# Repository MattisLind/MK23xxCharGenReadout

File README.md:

# Mostek MK23XX Character Generator Readout

This device is used to read out the contents of early character generator MK23XX ROMs from Mostek. These devices is a bit special since they include a column counter so that the each column cannot be
accessed directly through external addressing pins.

The device has to be connected over USB (unless this section is commented out in the source code) and then it provide a dump of the contents of the ROM as hex as it cycles through all 64 characters.

```
CHAR0 COLUMN 0 VALUE 0
CHAR0 COLUMN 1 VALUE 0
CHAR0 COLUMN 2 VALUE 0
CHAR0 COLUMN 3 VALUE 0
CHAR0 COLUMN 4 VALUE 0
CHAR1 COLUMN 0 VALUE 7
CHAR1 COLUMN 1 VALUE 7
CHAR1 COLUMN 2 VALUE 7
CHAR1 COLUMN 3 VALUE 7
CHAR1 COLUMN 4 VALUE 7
CHAR2 COLUMN 0 VALUE 70
CHAR2 COLUMN 1 VALUE 70
CHAR2 COLUMN 2 VALUE 70
CHAR2 COLUMN 3 VALUE 70
CHAR2 COLUMN 4 VALUE 70
```

Please note that the contents of this example ROM is active low so that a binary 0 indicate a lit pixel. Depending if the outputs are active low or high the output driver can be 7407 or 7406 respectively.

## PCB

The first PCB had too small holes for the 24 pin ROM socket so it was not possible to fit a ZIF socket. I revised the PCB so that the new PCB have 1.0 mm holes rather than 0.8 mm. I think that this should work better but have not ordered any PCB to check. 

## Software

The software is an Arduino sketch. I have been using [Arduino Core STM32](https://github.com/stm32duino/Arduino_Core_STM32) library. The Bluepill is a STM32F103C6 and it is set to have USB enabled with serial support 

There is a #define SCROLL which can be set to either 0 or 1 if one want the fancier soft scroll rather than just showing each character.

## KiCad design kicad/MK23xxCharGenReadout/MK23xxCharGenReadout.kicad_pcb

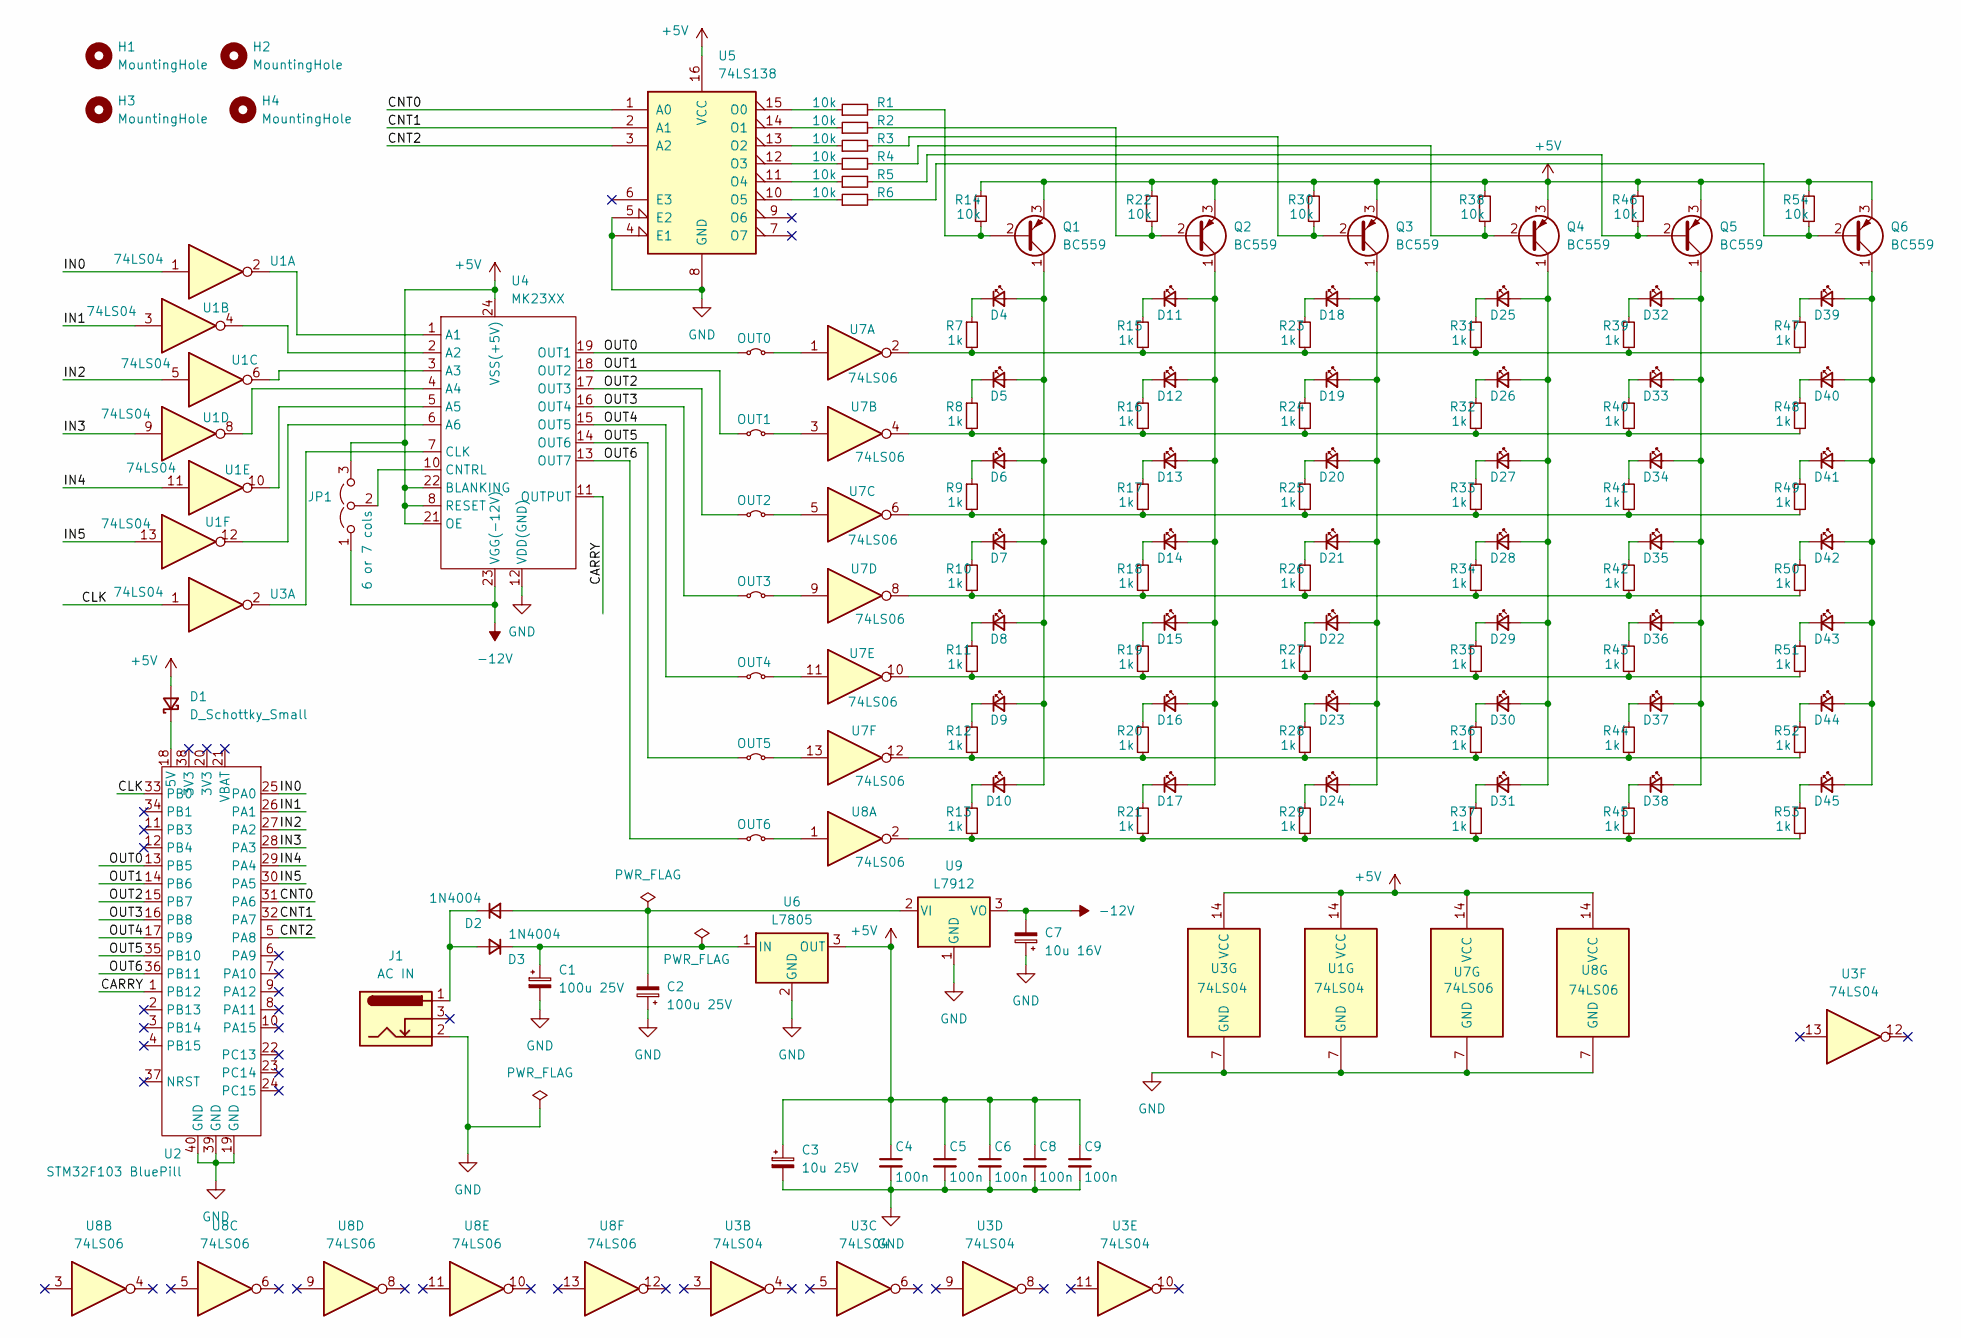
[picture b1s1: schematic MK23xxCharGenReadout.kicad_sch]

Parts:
C1, C2: 100u 25V; CP_Radial_D8.0mm_P5.00mm
C3: 10u 25V; CP_Radial_D7.5mm_P2.50mm
C4, C5, C6, C8, C9: 100n; C_Disc_D5.0mm_W2.5mm_P5.00mm
C7: 10u 16V; CP_Radial_D7.5mm_P2.50mm
D1: D_Schottky_Small; D_DO-41_SOD81_P10.16mm_Horizontal
D2, D3: 1N4004; D_DO-41_SOD81_P10.16mm_Horizontal
D4, D5, D6, D7, D8, D9, D10, D11, D12, D13, D14, D15, D16, D17, D18, D19, D20, D21, D22, D23, D24, D25, D26, D27, D28, D29, D30, D31, D32, D33, D34, D35, D36, D37, D38, D39, D40, D41, D42, D43, D44, D45: LED_Small; LED_D5.0mm
H1, H2, H3, H4: MountingHole; MountingHole_3.2mm_M3
J1: AC IN; BarrelJack_Kycon_KLDX-0202-xC_Horizontal
JP1: 6 or 7 cols; PinHeader_1x03_P2.54mm_Vertical
OUT0, OUT1, OUT2, OUT3, OUT4, OUT5, OUT6: Jumper_2_Small_Bridged; PinHeader_1x02_P2.54mm_Vertical
Q1, Q2, Q3, Q4, Q5, Q6: BC559; TO-92
R1, R2, R3, R4, R5, R6, R14, R22, R30, R38, R46, R54: 10k; R_Axial_DIN0207_L6.3mm_D2.5mm_P7.62mm_Horizontal
R7, R8, R9, R10, R11, R12, R13, R15, R16, R17, R18, R19, R20, R21, R23, R24, R25, R26, R27, R28, R29, R31, R32, R33, R34, R35, R36, R37, R39, R40, R41, R42, R43, R44, R45, R47, R48, R49, R50, R51, R52, R53: 1k; R_Axial_DIN0207_L6.3mm_D2.5mm_P7.62mm_Horizontal
U1, U3: 74LS04; DIP-14_W7.62mm
U2: STM32F103 BluePill; DIP-40_W15.24mm
U4: MK23XX; DIP-24_W15.24mm
U5: 74LS138; DIP-16_W7.62mm
U6: L7805; TO-220-3_Vertical
U7, U8: 74LS06; DIP-14_W7.62mm
U9: L7912; TO-220-3_Vertical

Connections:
+5V: C3.1, C4.1, C5.1, C6.1, C8.1, C9.1, D1.2 (A), JP1.3 (B), Q1.3 (E), Q2.3 (E), Q3.3 (E), Q4.3 (E), Q5.3 (E), Q6.3 (E), R14.1, R22.1, R30.1, R38.1, R46.1, R54.1, U1.14 (VCC), U3.14 (VCC), U4.8 (RESET), U4.21 (OE), U4.22 (BLANKING), U4.24 (VSS(+5V)), U5.16 (VCC), U6.3 (OUT), U7.14 (VCC), U8.14 (VCC)
-12V: C7.2, JP1.1 (A), U4.23 (VGG(-12V)), U9.3 (VO)
/CARRY: U2.1 (PB12), U4.11 (OUTPUT)
/CLK: U2.33 (PB0), U3.1
/CNT0: U2.31 (PA6), U5.1 (A0)
/CNT1: U2.32 (PA7), U5.2 (A1)
/CNT2: U2.5 (PA8), U5.3 (A2)
/IN0: U1.1, U2.25 (PA0)
/IN1: U1.3, U2.26 (PA1)
/IN2: U1.5, U2.27 (PA2)
/IN3: U1.9, U2.28 (PA3)
/IN4: U1.11, U2.29 (PA4)
/IN5: U1.13, U2.30 (PA5)
/OUT0: OUT0.1 (A), U2.13 (PB5), U4.19 (OUT1)
/OUT1: OUT1.1 (A), U2.14 (PB6), U4.18 (OUT2)
/OUT2: OUT2.1 (A), U2.15 (PB7), U4.17 (OUT3)
/OUT3: OUT3.1 (A), U2.16 (PB8), U4.16 (OUT4)
/OUT4: OUT4.1 (A), U2.17 (PB9), U4.15 (OUT5)
/OUT5: OUT5.1 (A), U2.35 (PB10), U4.14 (OUT6)
/OUT6: OUT6.1 (A), U2.36 (PB11), U4.13 (OUT7)
GND: C1.2, C2.1, C3.2, C4.2, C5.2, C6.2, C7.1, C8.2, C9.2, J1.2, U1.7 (GND), U2.19 (GND), U2.39 (GND), U2.40 (GND), U3.7 (GND), U4.12 (VDD(GND)), U5.4 (E1), U5.5 (E2), U5.8 (GND), U6.2 (GND), U7.7 (GND), U8.7 (GND), U9.1 (GND)
unnamed: D1.1 (K), U2.18 (5V)
unnamed: C2.2, D2.2 (A), U9.2 (VI)
unnamed: D2.1 (K), D3.2 (A), J1.1
unnamed: C1.1, D3.1 (K), U6.1 (IN)
unnamed: D4.1 (K), R7.1
unnamed: D5.1 (K), R8.1
unnamed: D6.1 (K), R9.1
unnamed: D7.1 (K), R10.1
unnamed: D8.1 (K), R11.1
unnamed: D9.1 (K), R12.1
unnamed: D4.2 (A), D5.2 (A), D6.2 (A), D7.2 (A), D8.2 (A), D9.2 (A), D10.2 (A), Q1.1 (C)
unnamed: D10.1 (K), R13.1
unnamed: D11.2 (A), D12.2 (A), D13.2 (A), D14.2 (A), D15.2 (A), D16.2 (A), D17.2 (A), Q2.1 (C)
unnamed: D11.1 (K), R15.1
unnamed: D12.1 (K), R16.1
unnamed: D13.1 (K), R17.1
unnamed: D14.1 (K), R18.1
unnamed: D15.1 (K), R19.1
unnamed: D16.1 (K), R20.1
unnamed: D17.1 (K), R21.1
unnamed: D18.2 (A), D19.2 (A), D20.2 (A), D21.2 (A), D22.2 (A), D23.2 (A), D24.2 (A), Q3.1 (C)
unnamed: D18.1 (K), R23.1
unnamed: D19.1 (K), R24.1
unnamed: D20.1 (K), R25.1
unnamed: D21.1 (K), R26.1
unnamed: D22.1 (K), R27.1
unnamed: D23.1 (K), R28.1
unnamed: D24.1 (K), R29.1
unnamed: D25.2 (A), D26.2 (A), D27.2 (A), D28.2 (A), D29.2 (A), D30.2 (A), D31.2 (A), Q4.1 (C)
unnamed: D25.1 (K), R31.1
unnamed: D26.1 (K), R32.1
unnamed: D27.1 (K), R33.1
unnamed: D28.1 (K), R34.1
unnamed: D29.1 (K), R35.1
unnamed: D30.1 (K), R36.1
unnamed: D31.1 (K), R37.1
unnamed: D32.2 (A), D33.2 (A), D34.2 (A), D35.2 (A), D36.2 (A), D37.2 (A), D38.2 (A), Q5.1 (C)
unnamed: D32.1 (K), R39.1
unnamed: D33.1 (K), R40.1
unnamed: D34.1 (K), R41.1
unnamed: D35.1 (K), R42.1
unnamed: D36.1 (K), R43.1
unnamed: D37.1 (K), R44.1
unnamed: D38.1 (K), R45.1
unnamed: D39.2 (A), D40.2 (A), D41.2 (A), D42.2 (A), D43.2 (A), D44.2 (A), D45.2 (A), Q6.1 (C)
unnamed: D39.1 (K), R47.1
unnamed: D40.1 (K), R48.1
unnamed: D41.1 (K), R49.1
unnamed: D42.1 (K), R50.1
unnamed: D43.1 (K), R51.1
unnamed: D44.1 (K), R52.1
unnamed: D45.1 (K), R53.1
unnamed: JP1.2 (C), U4.10 (CNTRL)
unnamed: OUT0.2 (B), U7.1
unnamed: OUT1.2 (B), U7.3
unnamed: OUT2.2 (B), U7.5
unnamed: OUT3.2 (B), U7.9
unnamed: OUT4.2 (B), U7.11
unnamed: OUT5.2 (B), U7.13
unnamed: OUT6.2 (B), U8.1
unnamed: Q1.2 (B), R1.2, R14.2
unnamed: Q2.2 (B), R2.2, R22.2
unnamed: Q3.2 (B), R3.2, R30.2
unnamed: Q4.2 (B), R4.2, R38.2
unnamed: Q5.2 (B), R5.2, R46.2
unnamed: Q6.2 (B), R6.2, R54.2
unnamed: R10.2, R18.2, R26.2, R34.2, R42.2, R50.2, U7.8
unnamed: R11.2, R19.2, R27.2, R35.2, R43.2, R51.2, U7.10
unnamed: R12.2, R20.2, R28.2, R36.2, R44.2, R52.2, U7.12
unnamed: R13.2, R21.2, R29.2, R37.2, R45.2, R53.2, U8.2
unnamed: R7.2, R15.2, R23.2, R31.2, R39.2, R47.2, U7.2
unnamed: R8.2, R16.2, R24.2, R32.2, R40.2, R48.2, U7.4
unnamed: R9.2, R17.2, R25.2, R33.2, R41.2, R49.2, U7.6
unnamed: U1.2, U4.1 (A1)
unnamed: U1.4, U4.2 (A2)
unnamed: U1.6, U4.3 (A3)
unnamed: U1.8, U4.4 (A4)
unnamed: U1.10, U4.5 (A5)
unnamed: U1.12, U4.6 (A6)
unnamed: U3.2, U4.7 (CLK)
unnamed: R1.1, U5.15 (O0)
unnamed: R2.1, U5.14 (O1)
unnamed: R3.1, U5.13 (O2)
unnamed: R4.1, U5.12 (O3)
unnamed: R5.1, U5.11 (O4)
unnamed: R6.1, U5.10 (O5)

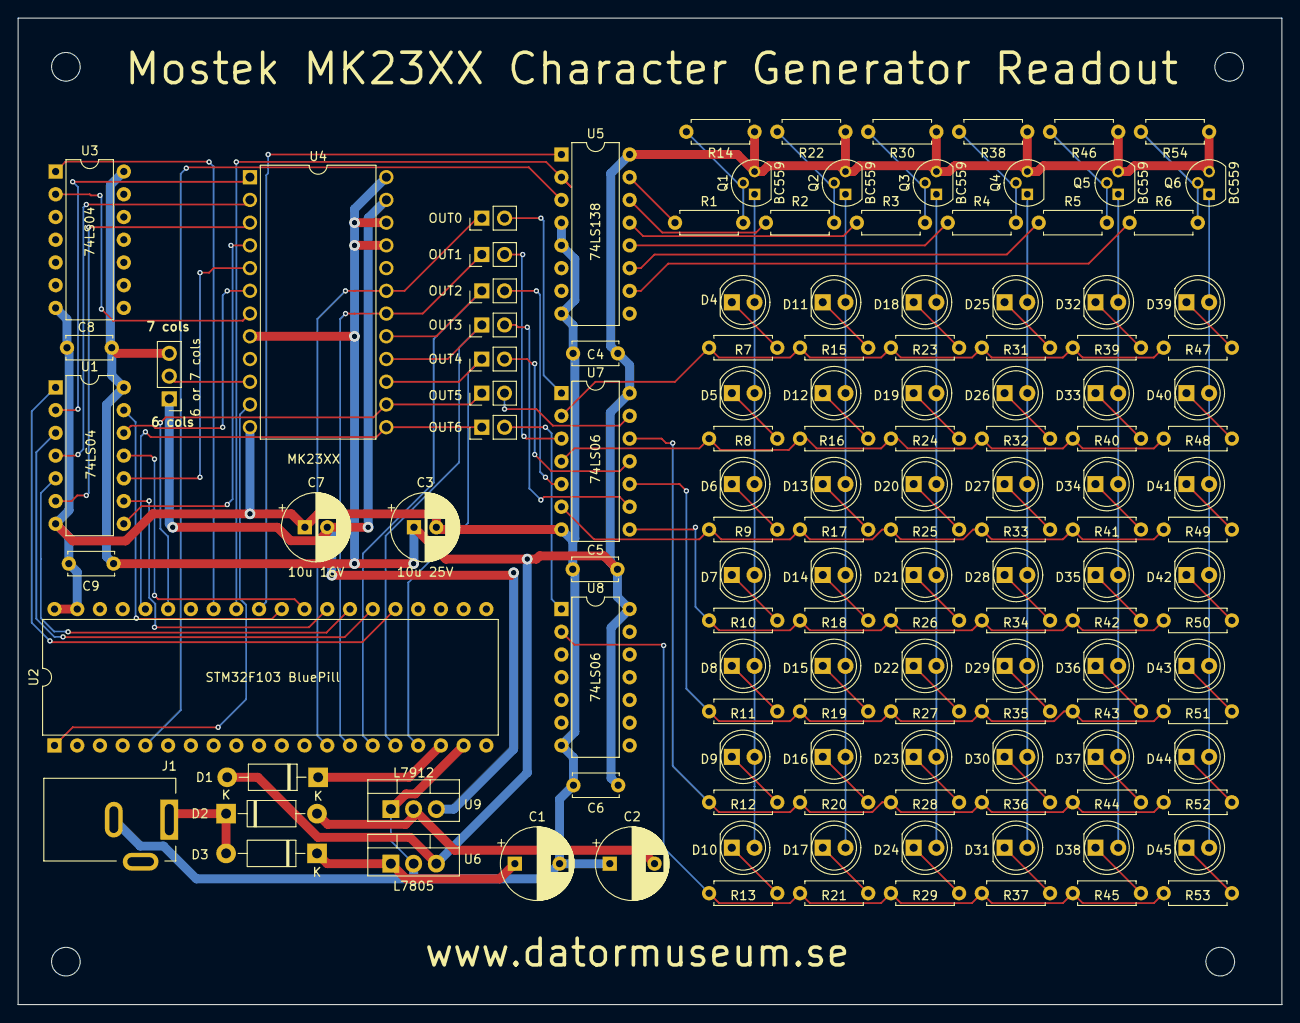
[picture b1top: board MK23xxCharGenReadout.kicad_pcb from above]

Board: 2 copper layers, 141.2 x 110.2 mm, 136 parts (0 on the bottom side), 107 nets.

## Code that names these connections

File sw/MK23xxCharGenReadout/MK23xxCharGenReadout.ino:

/*
  Sketch to read out and display the contents of a Mostek MK23xx Character Generatror ROM

  Mattis Lind 2025
*/

#define CLK PB0
#define CNT0 PA6
#define CNT1 PA7
#define CNT2 PA8
#define CARRY PB12
#define OUT0 PB5
#define OUT1 PB6
#define OUT2 PB7
#define OUT3 PB8
#define OUT4 PB9
#define OUT5 PB10
#define OUT6 PB11
#define IN0 PA0
#define IN1 PA1
#define IN2 PA2
#define IN3 PA3
#define IN4 PA4
#define IN5 PA5
#define SCROLL 0

void inOutput(int in) {
  digitalWrite(IN0, in & 1);
  digitalWrite(IN1, (in & 2)>>1);
  digitalWrite(IN2, (in & 4)>>2);
  digitalWrite(IN3, (in & 8)>>3);
  digitalWrite(IN4, (in & 16)>>4);
  digitalWrite(IN5, (in & 32)>>5);
}

int outRead() {
  return (digitalRead(OUT0)) | 
        ((digitalRead(OUT1)) << 1) |
        ((digitalRead(OUT2)) << 2) |
        ((digitalRead(OUT3)) << 3) |
        ((digitalRead(OUT4)) << 4) |
        ((digitalRead(OUT5)) << 5) |
        ((digitalRead(OUT6)) << 6);
}

void countOutput(int cnt) {
  int val;
  
  switch (cnt) {
    case 0:
      GPIOA ->ODR &= ~(GPIO_ODR_ODR6 | GPIO_ODR_ODR7 | GPIO_ODR_ODR8);
      break;
    case 1:
      GPIOA ->ODR &= ~(GPIO_ODR_ODR7 | GPIO_ODR_ODR8);
      GPIOA ->ODR |= (GPIO_ODR_ODR6);
      break;
    case 2:
      GPIOA ->ODR |= (GPIO_ODR_ODR7);
      GPIOA ->ODR &= ~(GPIO_ODR_ODR6 | GPIO_ODR_ODR8);   
      break;
    case 3:
      GPIOA ->ODR |= (GPIO_ODR_ODR6 | GPIO_ODR_ODR7);
      GPIOA ->ODR &= ~(GPIO_ODR_ODR8);    
      break;
    case 4:
      GPIOA ->ODR |= (GPIO_ODR_ODR8);
      GPIOA ->ODR &= ~(GPIO_ODR_ODR6  | GPIO_ODR_ODR7 );     
      break;
    case 5:
      GPIOA ->ODR |= (GPIO_ODR_ODR6  | GPIO_ODR_ODR8);
      GPIOA ->ODR &= ~(GPIO_ODR_ODR7 );    
      break;
    case 6:
      GPIOA ->ODR |= (GPIO_ODR_ODR7  | GPIO_ODR_ODR8);
      GPIOA ->ODR &= ~(GPIO_ODR_ODR6 );    
      break;      
    default:
      GPIOA ->ODR |= (GPIO_ODR_ODR6  | GPIO_ODR_ODR8 | GPIO_ODR_ODR7);   
      break;
  }
  
}

int i;
int j;
int character;
int k;
int start;

// the setup function runs once when you press reset or power the board
void setup() {
  pinMode(CNT0, OUTPUT);
  pinMode(CNT1, OUTPUT);
  pinMode(CNT2, OUTPUT);  
  pinMode(IN0, OUTPUT);
  pinMode(IN1, OUTPUT);
  pinMode(IN2, OUTPUT);
  pinMode(IN3, OUTPUT);
  pinMode(IN4, OUTPUT);
  pinMode(IN5, OUTPUT);
  pinMode(OUT0, INPUT);     
  pinMode(OUT1, INPUT); 
  pinMode(OUT2, INPUT); 
  pinMode(OUT3, INPUT); 
  pinMode(OUT4, INPUT); 
  pinMode(OUT5, INPUT); 
  pinMode(OUT6, INPUT);   
  pinMode(CARRY, INPUT);
  pinMode(CLK, OUTPUT);      
  i=0;
  j=0;
  k=0;
  character = 0;
  start=5;
  Serial.begin(9600);
  while (!Serial) {
    ;  // wait for serial port to connect. Needed for native USB port only
  }
  Serial.println("MK23XX CHAR GEN BIT MAP");
}


#define LEDPWM 100
#define CLK_LOW 500
#define CLK_HIGH 500
// the loop function runs over and over again forever
void loop() {
  //
  countOutput(7);
  digitalWrite(CLK, HIGH); 
  countOutput(7);
  delayMicroseconds(CLK_HIGH-LEDPWM); 
  countOutput(i);

  i++; 
  if (i>5) i=0; 
  if (k==0 && start == 0 && i > 0) {
    Serial.print("CHAR");
    Serial.print(character,HEX);
    Serial.print(" COLUMN ");
    Serial.print(((i-1)>=0)?(i-1):5);
    Serial.print(" VALUE ");
    Serial.print(outRead(), HEX);
    Serial.println();
  }

  delayMicroseconds(LEDPWM); 
  countOutput(6);
  digitalWrite(CLK, LOW);
  if (digitalRead(CARRY) == HIGH) {
    if (k>20) {
      start--;
      if (start<0) {
        start=5;
        if (character > 62) {
          character = 0;
        } else {
          character++;
        }
      }
      k=0;
    } else {
      k++;
    }
    if (SCROLL) {
      i = start;
    } else {
      i=0;
    }
  } 

  if (SCROLL) {
    if (i<start) {
      inOutput(~(character & 0x3f));  
    } else {
      inOutput(~((character+1) & 0x3f));  
    }
  } else {
    inOutput(~(character & 0x3f)); 
  } 

  delayMicroseconds(CLK_LOW);        
}

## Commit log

2025-01-31 Add files.
2025-02-09 Add picture
2025-02-09 Datasheet
2025-02-09 Datasheet in pdf
2025-02-09 Added schematic pdf file.
2025-02-09 Increased size of holes for 24 pin socket to allow for ZIF socket.
2025-02-09 Updated comments section.
2025-02-09 Correcting values in the schematic.
